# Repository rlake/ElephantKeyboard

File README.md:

# Elephant Keyboard
USB-C Number Pad Mechanical Keyboard

Featuring hot-swap Kailh sockets and RGB LED lighting.

Based on [Adafruit KB2040](https://www.adafruit.com/product/5302)

Keyboard Layout
---------------

Number pad from [Keyboard Layout Editor](http://www.keyboard-layout-editor.com)

```
["Num Lock","/","*","-"],
[{a:4,f:3},"7\nHome","8\n↑","9\nPgUp",{h:2},"+"],
["4\n←","5","6\n→"],
["1\nEnd","2\n↓","3\nPgDn",{h:2},"Enter"],
[{w:2},"0\nIns",".\nDel"]
```

Panel from [Swill Plate & Case Builder](http://builder.swillkb.com)

Options:
* mx t3
* cherry only
* edge padding 2.5mm
* corners 2.5mm

Firmware
--------

Based on [KMK](https://github.com/KMKfw/kmk_firmware)

With the following CircuitPython versions:

```
adafruit-circuitpython-adafruit_kb2040-en_GB-7.3.3.uf2
adafruit-circuitpython-bundle-7.x-mpy-20230129.zip
```

And these library files in `lib`:

```
adafruit_pixelbuf.mpy
neopixel.mpy
```

Parts
-----

* 0805 500R resistor QTY 1 (YAGEO RC0805JR-07470RL)
* 0805 100nF capacitor QTY 18 (YAGEO CC0805KRX7R9BB104)
* SC-70-5 level shifter buffer QTY 1 (TI SN74LV1T34DCKR)
* SOD-123 diode QTY 17 (ST 1N4148W)
* Kailh hot-swap sockets QTY 17 (CPG151101S11) [AdaFruit](https://www.adafruit.com/product/4958)
* Neopixel LEDs QTY 17 (SK6812MINI-E) [AdaFruit](https://www.adafruit.com/product/4960)

Plus KB2040 and any mechanical pieces for case i.e. bumpers (3M SJ-5312) and user choice of key caps and switches etc.

Panel was laser cut and powder coated 0.063" 5052 Aluminium by [SendCutSend](https://sendcutsend.com)

Other case parts laser cut 0.118" Acrylic, 0.030" chipboard and powder coated 0.063" 5052 Aluminium.

And finally 12mm M3 nylon or plastic nuts and bolts.

Build
-----

License Information
-------------------
The hardware is released under [Creative Commons ShareAlike 4.0 International](https://creativecommons.org/licenses/by-sa/4.0/).

Distributed as-is; no warranty is given.

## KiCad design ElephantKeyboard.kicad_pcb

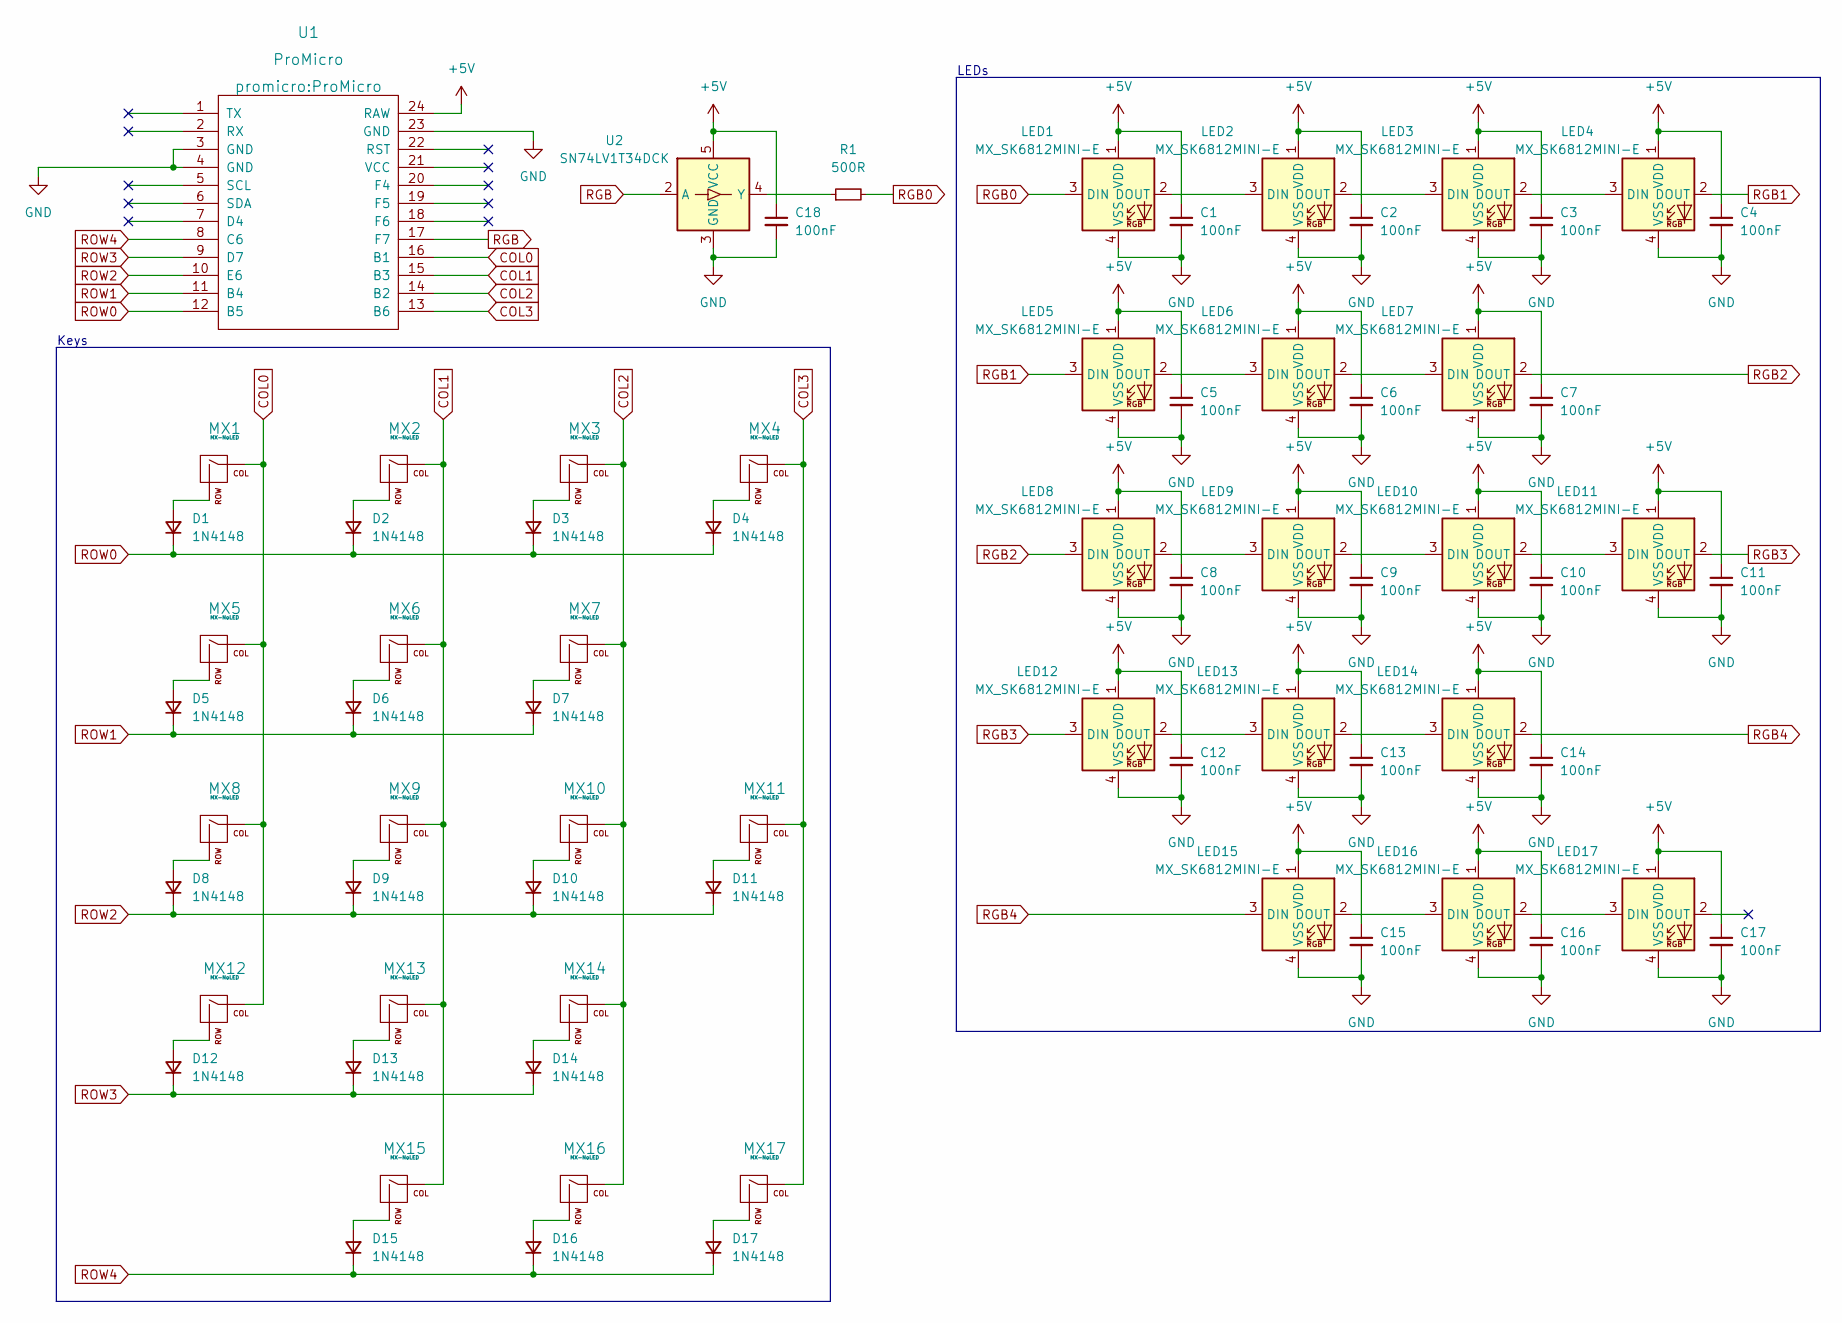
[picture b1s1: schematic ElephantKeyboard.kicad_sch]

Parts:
C1: 100nF
C2, C3, C4, C5, C6, C7, C8, C9, C10, C11, C12, C13, C14, C15, C16, C17, C18: 100nF; C_0805_2012Metric
D1: 1N4148
D2, D3, D4, D5, D6, D7, D8, D9, D10, D11, D12, D13, D14, D15, D16, D17: 1N4148; D_SOD-123
LED1, LED2, LED3, LED4, LED5, LED6, LED7, LED8, LED9, LED10, LED11, LED12, LED13, LED14, LED15, LED16, LED17: MX_SK6812MINI-E; LED_MX_6028R
MX1, MX2, MX3, MX4, MX5, MX6, MX7, MX8, MX9, MX10, MX12, MX13, MX14, MX16: MX-NoLED; MX-Hotswap-1U
MX11, MX17: MX-NoLED; MX-Hotswap-2U-Vertical
MX15: MX-NoLED; MX-Hotswap-2U
R1: 500R
U1: ProMicro
U2: SN74LV1T34DCK; SOT-353_SC-70-5

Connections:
+5V: C1.1, C2.1, C3.1, C4.1, C5.1, C6.1, C7.1, C8.1, C9.1, C10.1, C11.1, C12.1, C13.1, C14.1, C15.1, C16.1, C17.1, C18.1, LED1.1 (VDD), LED2.1 (VDD), LED3.1 (VDD), LED4.1 (VDD), LED5.1 (VDD), LED6.1 (VDD), LED7.1 (VDD), LED8.1 (VDD), LED9.1 (VDD), LED10.1 (VDD), LED11.1 (VDD), LED12.1 (VDD), LED13.1 (VDD), LED14.1 (VDD), LED15.1 (VDD), LED16.1 (VDD), LED17.1 (VDD), U1.24 (RAW), U2.5 (VCC)
COL0: MX1.1 (COL), MX5.1 (COL), MX8.1 (COL), MX12.1 (COL), U1.16 (B1)
COL1: MX2.1 (COL), MX6.1 (COL), MX9.1 (COL), MX13.1 (COL), MX15.1 (COL), U1.15 (B3)
COL2: MX3.1 (COL), MX7.1 (COL), MX10.1 (COL), MX14.1 (COL), MX16.1 (COL), U1.14 (B2)
COL3: MX4.1 (COL), MX11.1 (COL), MX17.1 (COL), U1.13 (B6)
GND: C1.2, C2.2, C3.2, C4.2, C5.2, C6.2, C7.2, C8.2, C9.2, C10.2, C11.2, C12.2, C13.2, C14.2, C15.2, C16.2, C17.2, C18.2, LED1.4 (VSS), LED2.4 (VSS), LED3.4 (VSS), LED4.4 (VSS), LED5.4 (VSS), LED6.4 (VSS), LED7.4 (VSS), LED8.4 (VSS), LED9.4 (VSS), LED10.4 (VSS), LED11.4 (VSS), LED12.4 (VSS), LED13.4 (VSS), LED14.4 (VSS), LED15.4 (VSS), LED16.4 (VSS), LED17.4 (VSS), U1.3 (GND), U1.4 (GND), U1.23 (GND), U2.3 (GND)
unnamed: D1.2 (A), MX1.2 (ROW)
unnamed: D4.2 (A), MX4.2 (ROW)
unnamed: D8.2 (A), MX8.2 (ROW)
unnamed: D9.2 (A), MX9.2 (ROW)
unnamed: D13.2 (A), MX13.2 (ROW)
unnamed: D15.2 (A), MX15.2 (ROW)
unnamed: LED1.2 (DOUT), LED2.3 (DIN)
unnamed: LED2.2 (DOUT), LED3.3 (DIN)
unnamed: LED3.2 (DOUT), LED4.3 (DIN)
unnamed: LED6.2 (DOUT), LED7.3 (DIN)
unnamed: LED5.2 (DOUT), LED6.3 (DIN)
unnamed: LED8.2 (DOUT), LED9.3 (DIN)
unnamed: LED10.2 (DOUT), LED11.3 (DIN)
unnamed: LED9.2 (DOUT), LED10.3 (DIN)
unnamed: LED12.2 (DOUT), LED13.3 (DIN)
unnamed: LED13.2 (DOUT), LED14.3 (DIN)
unnamed: LED15.2 (DOUT), LED16.3 (DIN)
unnamed: LED16.2 (DOUT), LED17.3 (DIN)
unnamed: D2.2 (A), MX2.2 (ROW)
unnamed: D3.2 (A), MX3.2 (ROW)
unnamed: D5.2 (A), MX5.2 (ROW)
unnamed: D6.2 (A), MX6.2 (ROW)
unnamed: D7.2 (A), MX7.2 (ROW)
unnamed: D10.2 (A), MX10.2 (ROW)
unnamed: D11.2 (A), MX11.2 (ROW)
unnamed: D12.2 (A), MX12.2 (ROW)
unnamed: D14.2 (A), MX14.2 (ROW)
unnamed: D16.2 (A), MX16.2 (ROW)
unnamed: D17.2 (A), MX17.2 (ROW)
unnamed: R1.1, U2.4 (Y)
RGB: U1.17 (F7), U2.2 (A)
RGB0: LED1.3 (DIN), R1.2
RGB1: LED4.2 (DOUT), LED5.3 (DIN)
RGB2: LED7.2 (DOUT), LED8.3 (DIN)
RGB3: LED11.2 (DOUT), LED12.3 (DIN)
RGB4: LED14.2 (DOUT), LED15.3 (DIN)
ROW0: D1.1 (K), D2.1 (K), D3.1 (K), D4.1 (K), U1.12 (B5)
ROW1: D5.1 (K), D6.1 (K), D7.1 (K), U1.11 (B4)
ROW2: D8.1 (K), D9.1 (K), D10.1 (K), D11.1 (K), U1.10 (E6)
ROW3: D12.1 (K), D13.1 (K), D14.1 (K), U1.9 (D7)
ROW4: D15.1 (K), D16.1 (K), D17.1 (K), U1.8 (C6)

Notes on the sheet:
Keys
LEDs

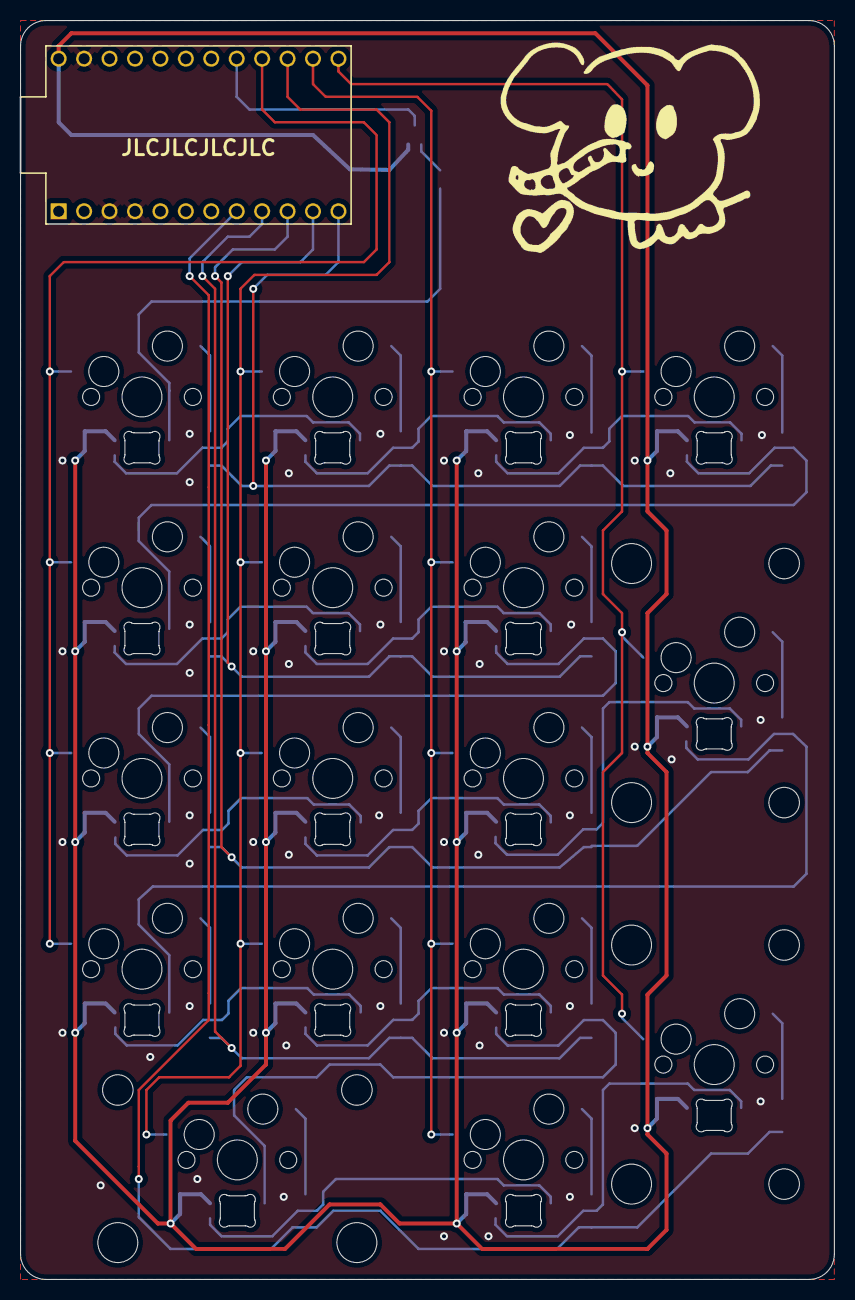
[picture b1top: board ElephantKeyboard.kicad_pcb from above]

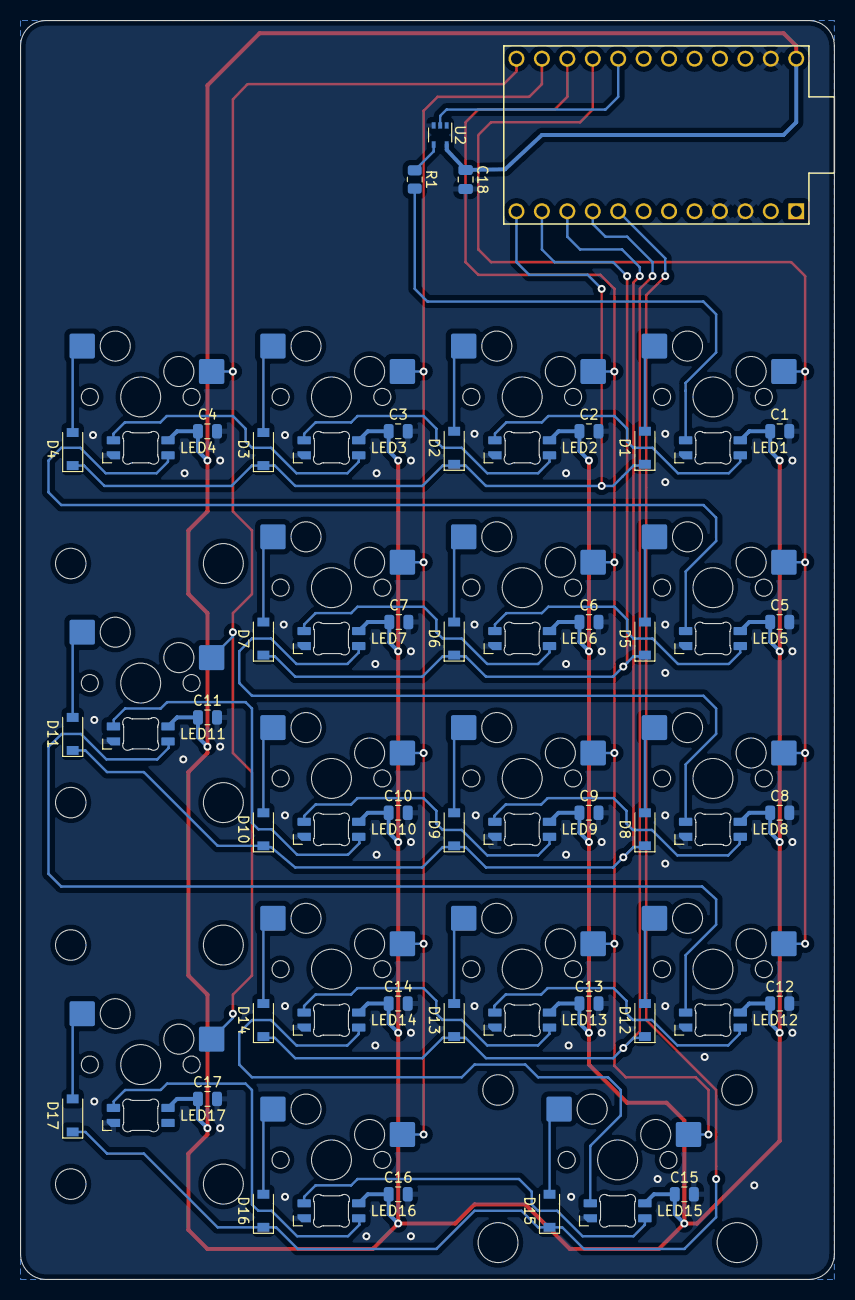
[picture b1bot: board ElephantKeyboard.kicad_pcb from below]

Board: 2 copper layers, 81.3 x 125.7 mm, 72 parts (54 on the bottom side), 47 nets.

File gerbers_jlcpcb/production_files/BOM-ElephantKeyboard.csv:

Comment,Designator,Footprint,LCSC
500R,R1,R_0805_2012Metric,C114747
100nF,"C1,C10,C11,C12,C13,C14,C15,C16,C17,C18,C2,C3,C4,C5,C6,C7,C8,C9",C_0805_2012Metric,C49678
SN74LV1T34DCK,U2,SOT-353_SC-70-5,C78541
1N4148,"D1,D10,D11,D12,D13,D14,D15,D16,D17,D2,D3,D4,D5,D6,D7,D8,D9",D_SOD-123,C81598

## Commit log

2023-01-22 Initial KiCad project
2023-01-22 ai03 MX legacy symbol library
2023-01-22 ai03 MX v2 footprint library
2023-01-22 ai03 ProMicro symbol and footprint library
2023-01-22 marbastlib symbol and footprint library
2023-01-28 Elephant Keyboard
2023-03-19 Schematics and PCB PDFs
2023-03-19 Gerbers
2023-03-19 Case design files
2023-03-20 Firmware files
2023-03-20 Images for PCB and build
